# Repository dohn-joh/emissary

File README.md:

***

Emissary is a 37-key wireless, alpha stagger keyboard with integrated lever keycaps.

[ZMK Module](https://github.com/dohn-joh/emissary-zmk-module)

[Case files](case)

[PCB](pcb)

***

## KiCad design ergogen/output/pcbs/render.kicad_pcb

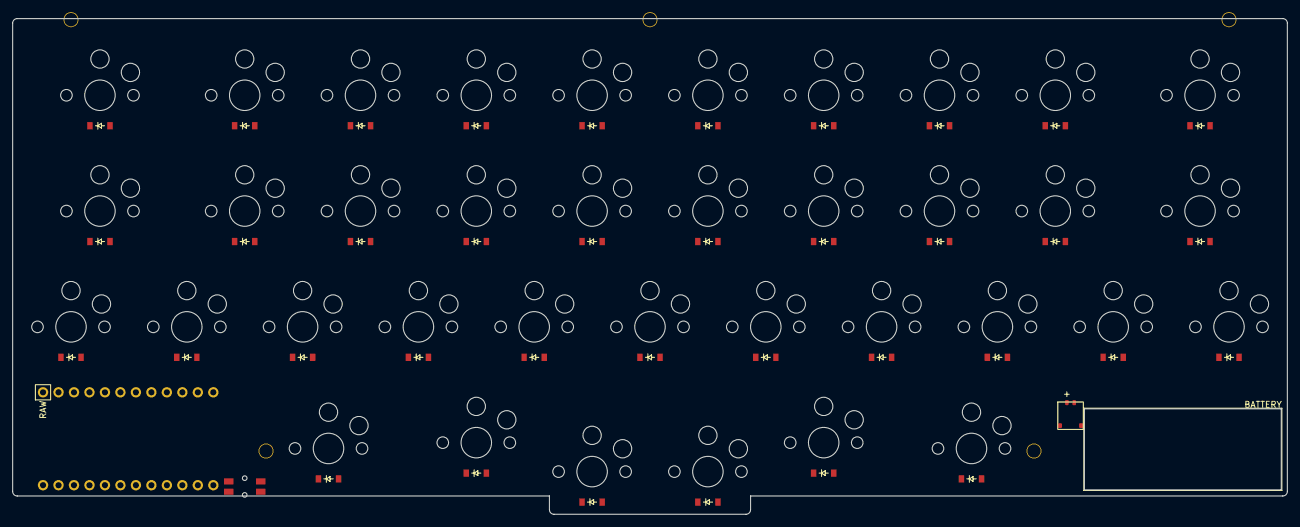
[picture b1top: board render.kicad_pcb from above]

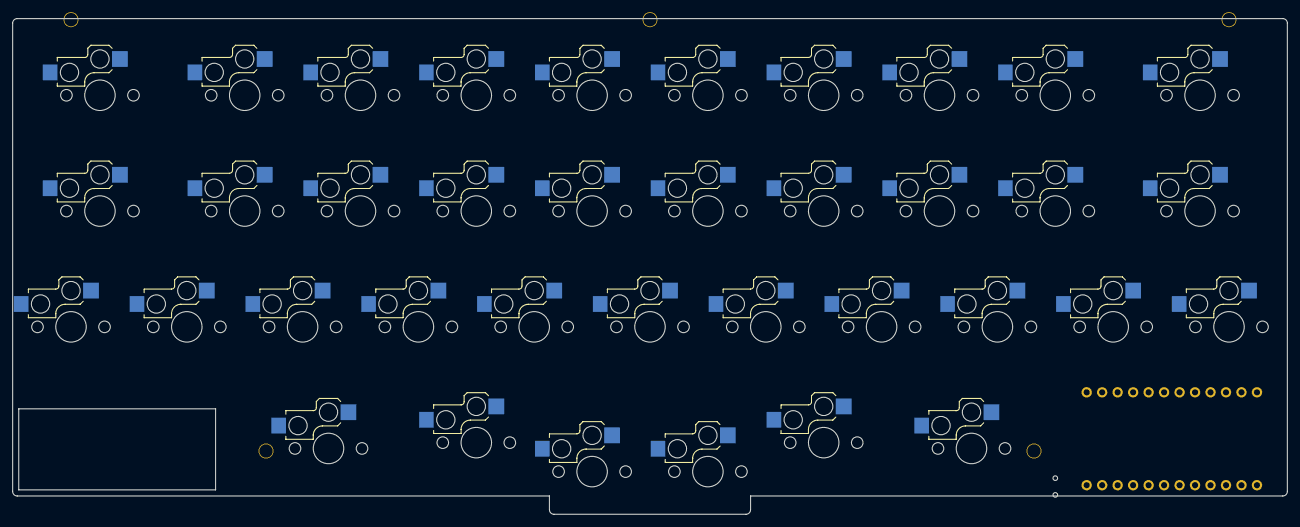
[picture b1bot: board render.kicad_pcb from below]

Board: 2 copper layers, 209.2 x 81.3 mm, 82 parts (37 on the bottom side), 48 nets, no tracks yet.

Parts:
CONN1: conn_molex_pico_front
D1, D2, D3, D4, D5, D6, D7, D8, D9, D10, D11, D12, D13, D14, D15, D16, D17, D18, D19, D20, D21, D22, D23, D24, D25, D26, D27, D28, D29, D30, D31, D32, D33, D34, D35, D36, D37: ComboDiode
H1, H2, H3, H4, H5: mounting_hole
MCU1: supermini_front
S1, S10: 1.5u_top
S2, S3, S4, S7, S8, S9: 1u_top
S5: 1u_top_tilted
S6: 1u_top_tilted_r
S11, S20: 1.5u_home
S12, S13, S14, S17, S18, S19: 1u_home
S15: 1u_home_tilted
S16: 1u_home_tilted_r
S21, S22, S23, S24, S25, S26, S27, S28, S29, S30, S31: 1u_bottom
S32, S37: switch_choc_v1_v2
S33, S34, S35, S36: 1u_convex
SW1: reset_button; sw_reset_side

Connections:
C1: MCU1.5, S1.1, S11.1, S22.1
C2: MCU1.6, S2.1, S12.1, S23.1
C3: MCU1.7, S3.1, S13.1, S24.1, S32.1
C4: MCU1.8, S4.1, S14.1, S25.1, S33.1
C5: MCU1.9, S5.1, S15.1, S26.1, S34.1
GND: CONN1.2, MCU1.2, MCU1.21, MCU1.22, SW1.1, SW1.3
R1: D1.1, D2.1, D3.1, D4.1, D5.1, D6.1, D7.1, D8.1, D9.1, D10.1, MCU1.18
R3: D11.1, D12.1, D13.1, D14.1, D15.1, D16.1, D17.1, D18.1, D19.1, D20.1, MCU1.16
R4: D21.1, D22.1, D23.1, D24.1, D25.1, D26.1, D27.1, D28.1, D29.1, D30.1, D31.1, MCU1.15
R5: D32.1, D33.1, D34.1, D35.1, D36.1, D37.1
RST: MCU1.3, SW1.2, SW1.4
a_home: D11.2, S11.2
b_bottom: D26.2, S26.2
base2_thumb: D36.2, S36.2
base_thumb: D33.2, S33.2
c_bottom: D24.2, S24.2
comma_bottom: D29.2, S29.2
d_home: D13.2, S13.2
dot_bottom: D30.2, S30.2
e_top: D3.2, S3.2
ext2_thumb: D35.2, S35.2
ext_thumb: D34.2, S34.2
extra_bottom: D21.2, S21.2
f_home: D14.2, S14.2
flex2_thumb: D37.2, S37.2
flex_thumb: D32.2, S32.2
g_home: D15.2, S15.2
h_home: D16.2, S16.2
i_top: D8.2, S8.2
j_home: D17.2, S17.2
k_home: D18.2, S18.2
l_home: D19.2, S19.2
m_bottom: D28.2, S28.2
n_bottom: D27.2, S27.2
o_top: D9.2, S9.2
p_top: D10.2, S10.2
q_top: D1.2, S1.2
r_top: D4.2, S4.2
s_home: D12.2, S12.2
semi_home: D20.2, S20.2
slash_bottom: D31.2, S31.2
t_top: D5.2, S5.2
u_top: D7.2, S7.2
v_bottom: D25.2, S25.2
w_top: D2.2, S2.2
x_bottom: D23.2, S23.2
y_top: D6.2, S6.2
z_bottom: D22.2, S22.2

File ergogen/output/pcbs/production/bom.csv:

Designator,Footprint,Quantity,Value,LCSC Part #
CONN1,conn_molex_pico_front,1,,
"D1, D10, D11, D12, D13, D14, D15, D16, D17, D18, D19, D2, D20, D21, D22, D23, D24, D25, D26, D27, D28, D29, D3, D30, D31, D32, D33, D34, D35, D36, D37, D4, D5, D6, D7, D8, D9",ComboDiode,37,,
"H1, H2, H3, H4, H5",mounting_hole,5,,
PAD1,battery_pads,1,,
SW1,sw_reset_side,1,reset_button,

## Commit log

2025-04-11 added case files, photos. cleanup files
2025-04-11 fix photos
2025-04-15 test
